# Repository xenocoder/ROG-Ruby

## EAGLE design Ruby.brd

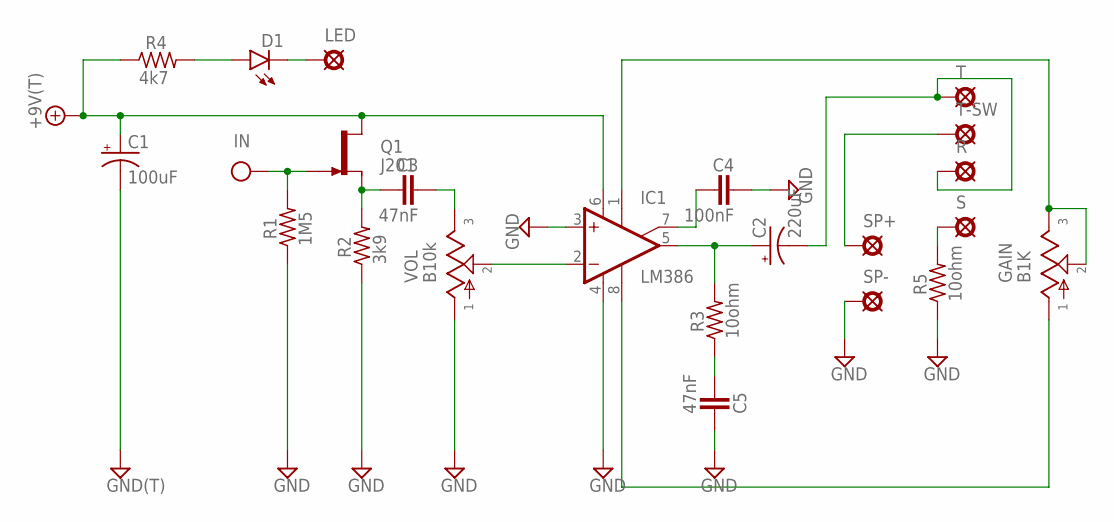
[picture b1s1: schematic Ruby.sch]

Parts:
+9V: +9V(T); SQUARE
C1: 100uF; 063_025
C2: 220uF; 080_035_1
C3, C5: 47nF; 072X035
C4: 100nF; 072X035
D1: LED3MM
GAIN: B1K; 16MM
GND: GND(T); SQUARE
IC1: LM386; DIL08
IN: IN(T); SQUARE
LED: PAD; SQUARE
Q1: J201; TO92-
R: PAD; SQUARE
R1: 1M5; R0207/3
R2: 3k9; R0207/3
R3, R5: 10ohm; R0207/3
R4: 4k7; R0207/3
S: PADO; ROUND
SP+: PAD; SQUARE
SP-: PADO; ROUND
T: PAD; SQUARE
T-SW: PAD; SQUARE
VOL: B10k; 16MM

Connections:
+9V: +9V.1, C1.+, IC1.6 (V+), Q1.3 (D), R4.1
GND: C1.-, C4.2, C5.2, GND.1, IC1.3 (+IN), IC1.4 (V-), R1.1, R2.1, R5.1, SP-.1, VOL.1
IN: IN.1, Q1.1 (G), R1.2
unnamed: D1.A, R4.2
unnamed: D1.K (C), LED.1
unnamed: C3.1, Q1.2 (S), R2.2
unnamed: C3.2, VOL.3
unnamed: IC1.2 (-IN), VOL.2
unnamed: C4.1, IC1.7 (BYPASS)
unnamed: C2.+, IC1.5 (OUT), R3.2
unnamed: C5.1, R3.1
unnamed: R5.2, S.1
unnamed: SP+.1, T-SW.1
unnamed: C2.-, R.1, T.1
unnamed: GAIN.2, GAIN.3, IC1.1 (GAIN1)
unnamed: GAIN.1, IC1.8 (GAIN2)

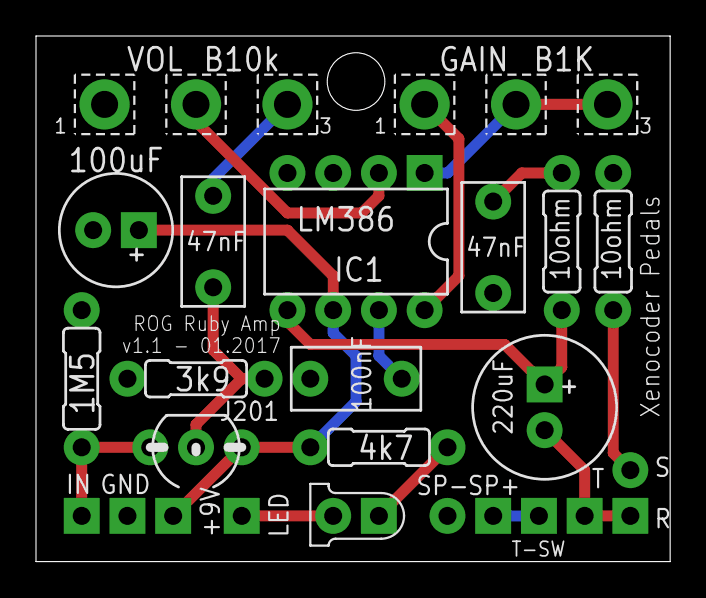
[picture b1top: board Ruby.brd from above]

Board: 2 copper layers, 35.2 x 29.2 mm, 25 parts (0 on the bottom side), 16 nets.

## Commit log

2017-01-06 First commit. Version 1.0 sent to OSHPark
2017-01-26 Fixed airier issue between speaker+ and headphone jack. Updated to v1.1
